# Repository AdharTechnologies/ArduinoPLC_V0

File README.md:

# ArduinoPLC_V0

#Description
This is an open-source PLC alternative board. This is still in its initial phase 

kindly read this blog for full understanding: https://docs.google.com/document/d/e/2PACX-1vQEhbrD9LXz9IJRHBPi5CLE20ouo7tDd4jXEcZmm0yRYeQ_W0wbrSWtcI1w_MdzkYJWM70-H2rYn1Xp/pub 

# Embedded CTG

Facebook:https://www.facebook.com/profile.php?id=61558436573900

Youtube: https://www.youtube.com/@EmbeddedCTG

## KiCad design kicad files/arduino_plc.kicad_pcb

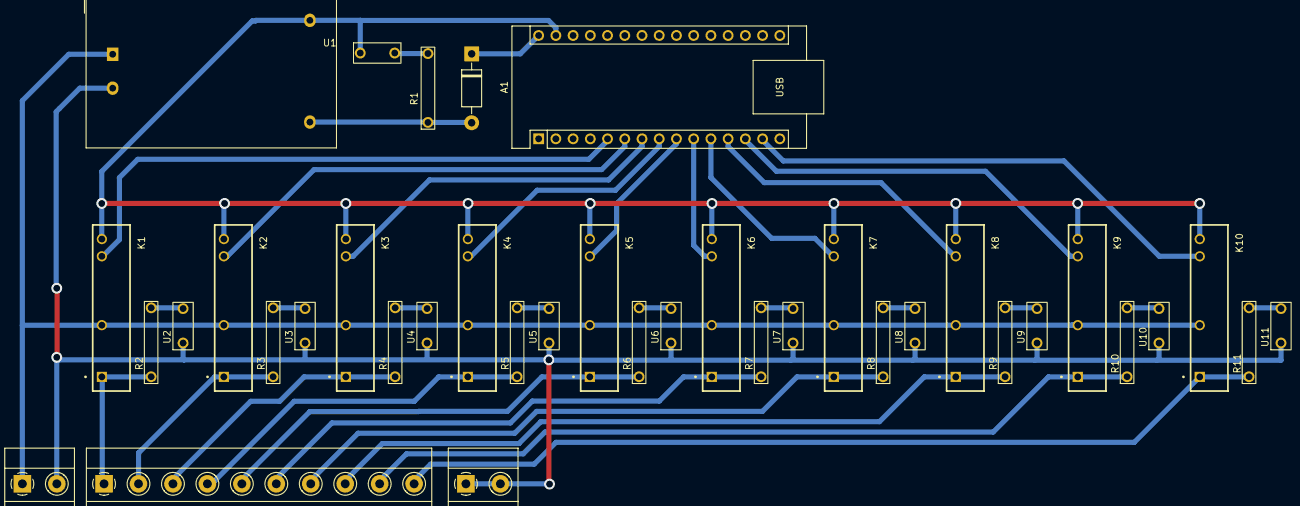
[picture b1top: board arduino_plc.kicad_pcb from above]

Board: 2 copper layers, 35 parts (0 on the bottom side), 36 nets.

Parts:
A1: Arduino_Nano_v3.x; Arduino_Nano
D1: 1N4007; D_DO-41_SOD81_P10.16mm_Horizontal
K1, K2, K3, K4, K5, K6, K7, K8, K9, K10: G3MB-202P; RELAY_G3MB-202P
PS1: HLK-PM01; Converter_ACDC_Hi-Link_HLK-PMxx
R1, R2, R3, R4, R5, R6, R7, R8, R9, R10, R11: 220; Resistor_A
U1, U2, U3, U4, U5, U6, U7, U8, U9, U10, U11: LED_A

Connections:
2: A1.5 (D2), K1.3
3: A1.6 (D3), K2.3
4: A1.7 (D4), K3.3
5: A1.8 (D5), K4.3
6: A1.9 (D6), K5.3
7: A1.10 (D7), K6.3
8: A1.11 (D8), K7.3
9: A1.12 (D9), K8.3
10: A1.13 (D10), K9.3
11: A1.14 (D11), K10.3
AC: K1.2, K2.2, K3.2, K4.2, K5.2, K6.2, K7.2, K8.2, K9.2, K10.2, PS1.1 (AC/L)
GND: A1.29 (GND), K1.4, K2.4, K3.4, K4.4, K5.4, K6.4, K7.4, K8.4, K9.4, K10.4, PS1.3 (-Vout), U1.1
NEUT: PS1.2 (AC/N), U2.1, U3.1, U4.1, U5.1, U6.1, U7.1, U8.1, U9.1, U10.1, U11.1
unnamed: D1.2 (A), PS1.4 (+Vout), R1.1
unnamed: K1.1, R2.1
unnamed: K2.1, R3.1
unnamed: K3.1, R4.1
unnamed: K4.1, R5.1
unnamed: K5.1, R6.1
unnamed: K6.1, R7.1
unnamed: K7.1, R8.1
unnamed: K8.1, R9.1
unnamed: K9.1, R10.1
unnamed: K10.1, R11.1
unnamed: R1.2, U1.2
unnamed: R2.2, U2.2
unnamed: R3.2, U3.2
unnamed: R4.2, U4.2
unnamed: R5.2, U5.2
unnamed: R6.2, U6.2
unnamed: R7.2, U7.2
unnamed: R8.2, U8.2
unnamed: R9.2, U9.2
unnamed: R10.2, U10.2
unnamed: R11.2, U11.2
VCC: A1.30 (VIN), D1.1 (K)

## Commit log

2025-03-11 Added windows executable file ArduinoPLCGUI.exe
2025-03-11 README.md
